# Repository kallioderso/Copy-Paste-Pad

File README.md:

# Copy-Paste-Pad
a Short Keyboard with **8 Keys**, **8 Diodes**, a small **OLED screen** and an [**Seeed XIAO RP2040**](https://wiki.seeedstudio.com/XIAO-RP2040/) on board. Developed for the purpose of unlocking the possibility to store up to 6 different Texts or other Things inside the memory, while keeping an overview and controlled usage of the stored elements.

## Schematic & PCB
The Board was deisgned in KiCAD as first of this kind experience for myself and included the mentioned [**Seeed XIAO RP2040**](https://wiki.seeedstudio.com/XIAO-RP2040/). There i connected the **8 Keys** and theire **8 Diodes** inside a *3 x 3* Key Matrix, as shown in a youtube tutorial by [ai03](https://wiki.ai03.com/books/pcb-design).

Apart from that i Added as wel a **OLED screen** to show wheather the Keyboard is currently in a ***Copy*** or a ***Paste*** state or if both false, in an displaying state. The OLED Screen is currently wired with the *5V* output of the [**Seeed XIAO RP2040**](https://wiki.seeedstudio.com/XIAO-RP2040/), but might be later reduced to the *3.3V* output. Apart from that its wired with the *GNU* which i learned, is to remove electicity from components, so the opposit of the Voltage outputs. Last but not Least is the **OLED screen** wired with the *SDA* and *SCL* pins.

In The following you can than see the finished **PCB** inside KiCAD, as well as its **3D Rendering**. Sadly i wasnt able to render the [**Seeed XIAO RP2040**](https://wiki.seeedstudio.com/XIAO-RP2040/) and the **8 Keys**, but at least the **8 Diodes** -_- .

## CAD / Casing
The Casing is one of the most important things of an Keyboard, as it determines wheather a Product will be loved or hated by an Community. but anyways did i keep a relativly ***simple*** design with rounded edges and a simple but effectiv order of the different **keys** and the **OLED screen**. In the following you can see first, the Bottom of the Casing, and after that the top, which later on will get fixed into the bottom half.

as wood is a great material, appearing in high quality and therefore more professional i as well created the entire ***bottom half*** of the casing as **.dxf** just as the ***top part***, which unfortunatly could just be made by a laser, as a CNC machine would struggle with the fine borders beetwheen each key switch.

## Firmware
besides all the hardware, the firmware is what makes a product standing out from others, therefore the mission was clear. 1 key to activate the so called *copying mode*, one other key to activate the *pasting mode*. both of which would **stay active** until you decide to deactivate them.

so the only remaining thing would be to press the wanted key switch for the different (out of **6**) clipboards.

to achieve this the keyboard needs both, a **own firmware**. as well as a **.exe Application** running on the PC himself to performe all the Copying and Pasting things the keyboard itself isnt allowed.

### QMK
the QMK firmware consists of the [v1](./Firmware/copy_paste_board/keymaps/v1/) keymap, presenting almost every smart thing and function in general provided by the keyboard. this gets underlined by the [rules](./Firmware/copy_paste_board/rules.mk) set to make working with **hid** (human interface device) and the **OLED screen** possible.

Last but not least is there the [keyboard info](./Firmware/copy_paste_board/keyboard.json) providing every basic information about the producer, its components and the **key matrix**, consisting of **Rows** and **Columns**

### Windows Application
the Womdpws Application in form of an **.exe** is where the fun begins. it gets **hid** (human interface device) signals by the QMK firmware, telling it what action to performe.

Whether its **Copying**, **Pasting** or just doing nothing, the **hid** is the source of decision.

to prevent the user from having to start this Script each time they start their PCs, it is so smart that it writes itself into the **Auto start** after the *first* execution of itself. making it possible to use the keyboard without any action.

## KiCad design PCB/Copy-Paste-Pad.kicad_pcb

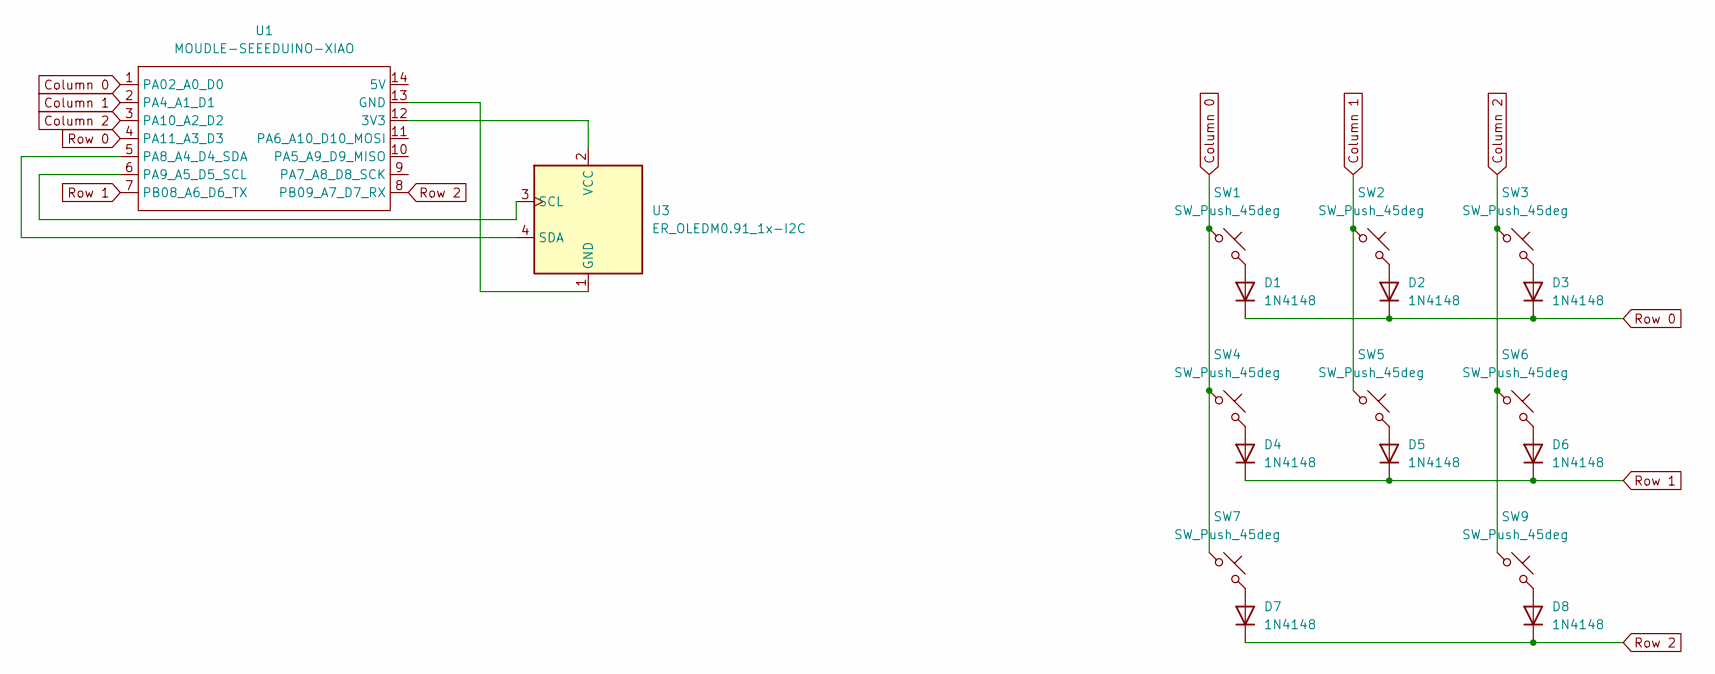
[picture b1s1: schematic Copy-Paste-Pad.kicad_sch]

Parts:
D1, D2, D3, D4, D5, D6, D7, D8: 1N4148; D_DO-35_SOD27_P7.62mm_Horizontal
SW1, SW2, SW3, SW4, SW5, SW6, SW7, SW9: SW_Push_45deg; SW_Cherry_MX_1.00u_PCB
U1: MOUDLE-SEEEDUINO-XIAO; XIAO-Generic-Hybrid-14P-2.54-21X17.8MM
U3: ER_OLEDM0.91_1x-I2C

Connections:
Column 0: SW1.1, SW4.1, SW7.1, U1.1 (PA02_A0_D0)
Column 1: SW2.1, SW5.1, U1.2 (PA4_A1_D1)
Column 2: SW3.1, SW6.1, SW9.1, U1.3 (PA10_A2_D2)
unnamed: D1.2 (A), SW1.2
unnamed: D2.2 (A), SW2.2
unnamed: D3.2 (A), SW3.2
unnamed: D4.2 (A), SW4.2
unnamed: D5.2 (A), SW5.2
unnamed: D6.2 (A), SW6.2
unnamed: D7.2 (A), SW7.2
unnamed: D8.2 (A), SW9.2
unnamed: U1.12 (3V3), U3.2 (VCC)
unnamed: U1.13 (GND), U3.1 (GND)
unnamed: U1.5 (PA8_A4_D4_SDA), U3.4 (SDA)
unnamed: U1.6 (PA9_A5_D5_SCL), U3.3 (SCL)
Row 0: D1.1 (K), D2.1 (K), D3.1 (K), U1.4 (PA11_A3_D3)
Row 1: D4.1 (K), D5.1 (K), D6.1 (K), U1.7 (PB08_A6_D6_TX)
Row 2: D7.1 (K), D8.1 (K), U1.8 (PB09_A7_D7_RX)

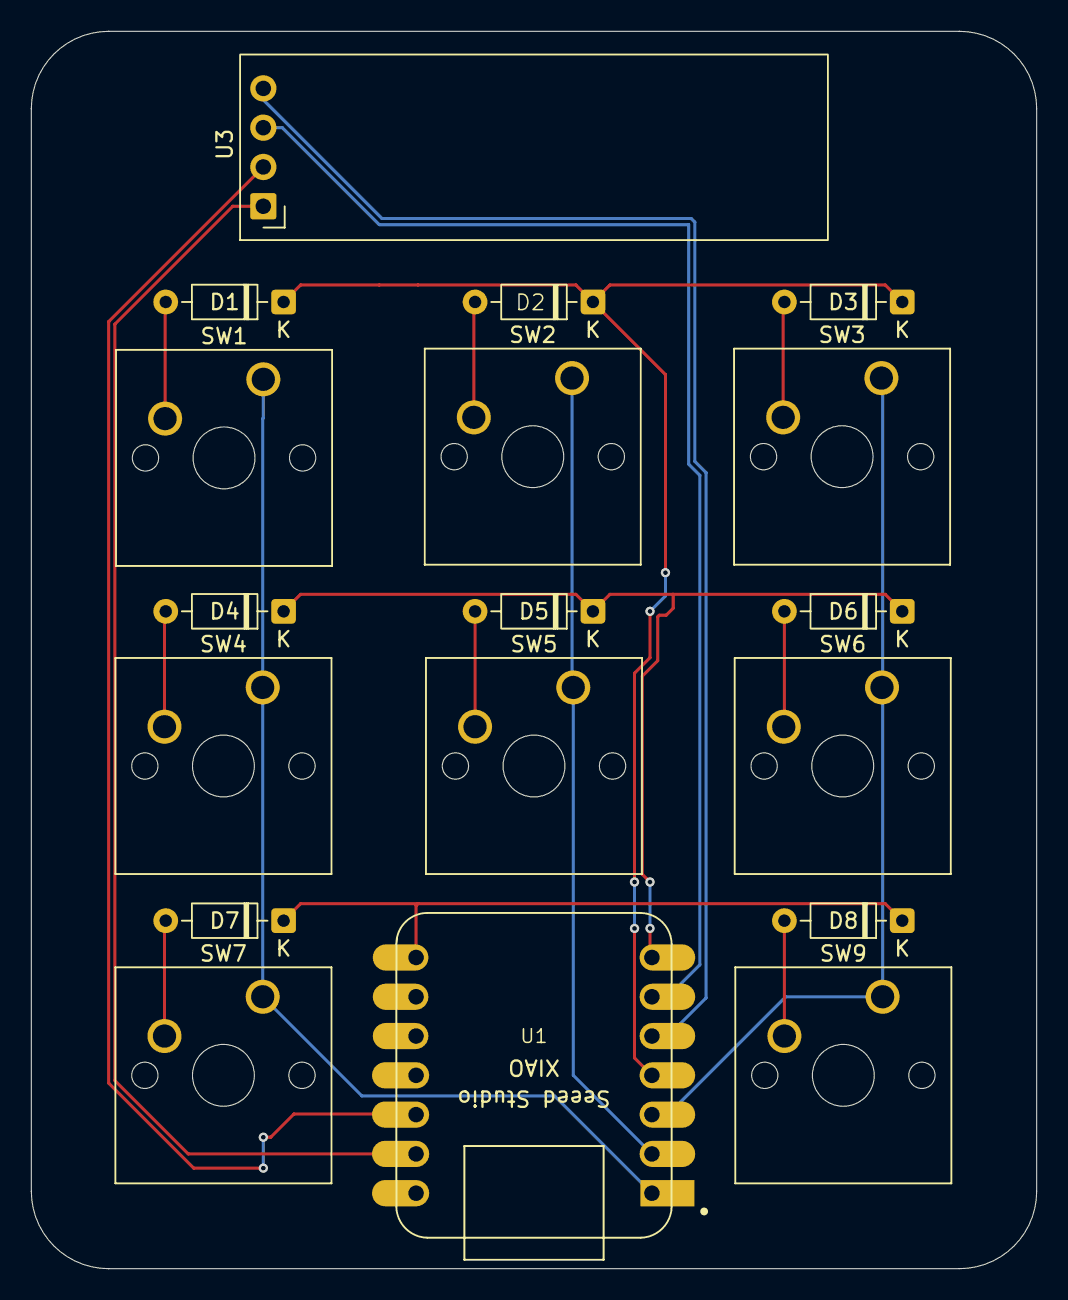
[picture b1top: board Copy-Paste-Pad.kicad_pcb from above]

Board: 2 copper layers, 65.0 x 80.0 mm, 18 parts (0 on the bottom side), 18 nets.
